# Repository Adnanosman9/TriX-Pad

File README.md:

<h1 align="center">
  TriXpad
</h1>

<h4 align="center">
  A custom, open-source mechanical macro-pad featuring an OLED screen.
</h4>

<div align="center">

</div>

<br>

##  Key Features

* **Brain:** Powered by the compact and capable **Seeed Studio XIAO RP2040**.
* **Firmware:** Runs on **KMK Firmware** (CircuitPython) for incredibly easy keymap customization without needing to recompile.
* **Display:** Integrated **0.91" SSD1306 OLED (128×64)** for real-time layer feedback, stats, or custom graphics.
* **Matrix:** A clean **3×3 Key Matrix** layout complete with diode orientation for robust anti-ghosting.

---

## Hardware Design

This project was built entirely from scratch, bridging custom PCB design with 3D modeling. 

### PCB (KiCad)
The board was routed and designed in KiCad to keep the footprint as minimal as possible while accommodating the XIAO RP2040 and OLED screen.

| Schematic | PCB Layout | 3D Render |
| :---: | :---: | :---: |
|  |  |  |

### Case (Fusion 360)
The enclosure was designed in Autodesk Fusion 360—marking my very first time diving into CAD! It features a sleek, two-part snap-fit/screw design to house the PCB and switches securely.

| Top Case | Bottom Case |
| :---: | :---: |
|  |  |

###  The Final Build
<div align="center">
  
</div>

---

##  Bill of Materials (BOM)

Everything you need to build this macro-pad yourself. *(For full details, see the [`BOM.csv`](BOM.csv) file).*

| Component | Description / Item | Qty | Source |
| :--- | :--- | :---: | :--- |
| **Controller** | Seeed Studio XIAO RP2040 | 1 | [AliExpress](https://www.aliexpress.com/item/1005003901735765.html) |
| **Switches** | MX-Style (Cherry) | 9 | [AliExpress](https://www.aliexpress.com/item/1005008656717678.html) |
| **Display** | 0.91" SSD1306 OLED | 1 | [AliExpress](https://www.aliexpress.com/item/1005009334190029.html) |
| **Diodes** | 1N4148 Through-Hole | 9 | [Robotics BD](https://store.roboticsbd.com/components/1355-1n4148-diode-robotics-bangladesh.html) |
| **Keycaps** | Blank DSA Keycaps (Black) | 9 | [AliExpress](https://www.aliexpress.com/item/1005006114411137.html) |

---

##  Credits & Acknowledgments

This project wouldn't be possible without these incredible open-source tools and communities:

* **[KiCad](https://www.kicad.org/)** for the phenomenal open-source PCB design suite.
* **[Autodesk Fusion 360](https://www.autodesk.com/products/fusion-360/)** for the case design environment.
* **[Hack Club Blueprint](https://blueprint.hackclub.com/)** for the guide and inspiration. 
* Massive thanks to **Hack Club Bank** for the grant that funded the PCB and case manufacturing to bring this hardware to life!

<br>

<div align="center">
  
  <br><br>
  <b>Designed by <a href="https://github.com/Adnanosman9">@Adnanosman</a></b>
</div>

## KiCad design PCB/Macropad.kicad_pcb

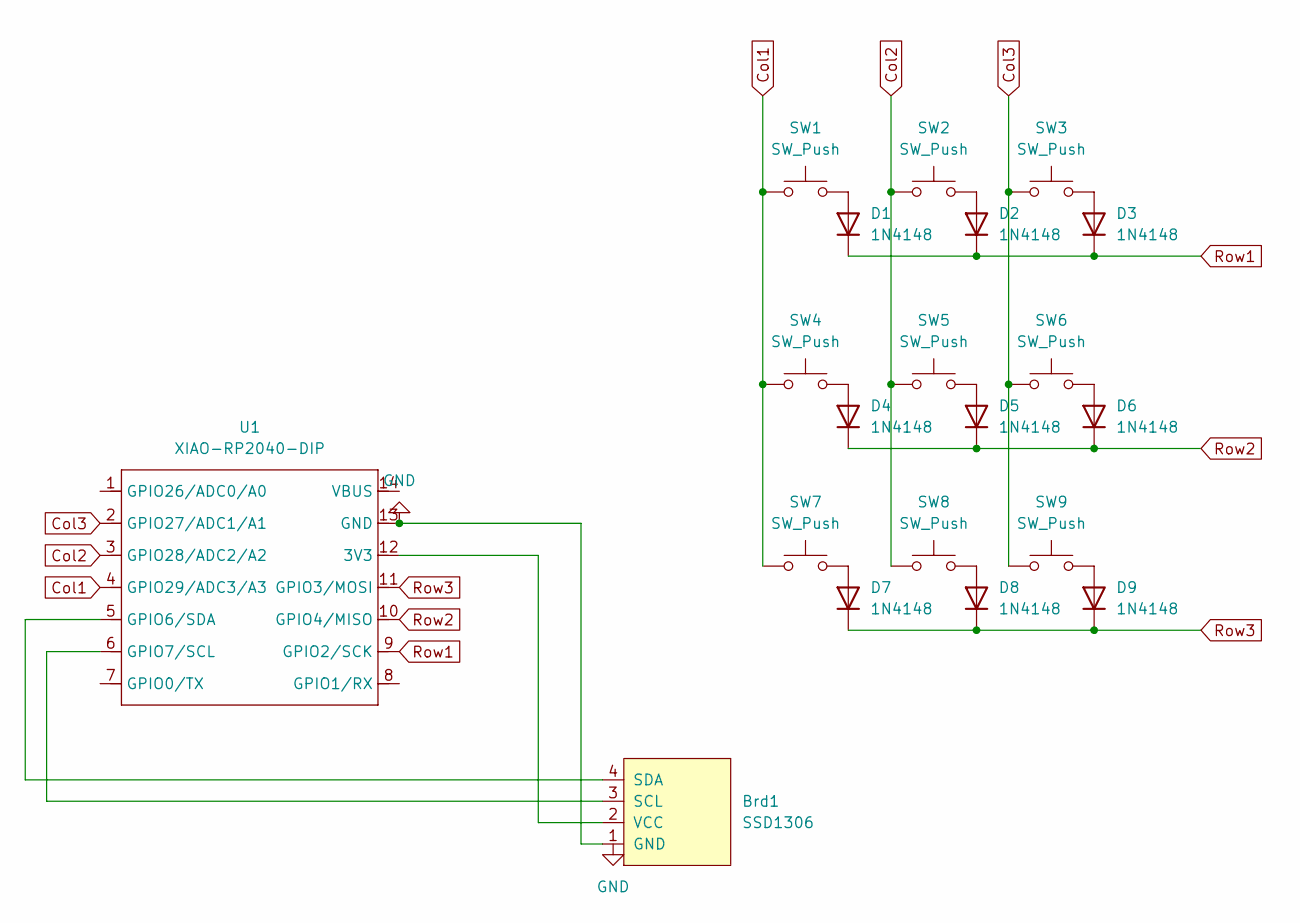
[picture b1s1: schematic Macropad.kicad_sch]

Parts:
Brd1: SSD1306; Adafruit_SSD1306
D1, D2, D3, D4, D5, D6, D7, D8, D9: 1N4148; D_DO-35_SOD27_P7.62mm_Horizontal
SW1, SW2, SW3, SW4, SW5, SW6, SW7, SW8, SW9: SW_Push; SW_Cherry_MX_1.00u_PCB
U1: XIAO-RP2040-DIP; Seeed_XIAO_RP2040

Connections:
Col1: SW1.1, SW4.1, SW7.1, U1.4 (GPIO29/ADC3/A3)
Col2: SW2.1, SW5.1, SW8.1, U1.3 (GPIO28/ADC2/A2)
Col3: SW3.1, SW6.1, SW9.1, U1.2 (GPIO27/ADC1/A1)
GND: Brd1.1 (GND), U1.13 (GND)
unnamed: Brd1.3 (SCL), U1.6 (GPIO7/SCL)
unnamed: Brd1.4 (SDA), U1.5 (GPIO6/SDA)
unnamed: Brd1.2 (VCC), U1.12 (3V3)
unnamed: D1.2 (A), SW1.2
unnamed: D2.2 (A), SW2.2
unnamed: D3.2 (A), SW3.2
unnamed: D4.2 (A), SW4.2
unnamed: D5.2 (A), SW5.2
unnamed: D6.2 (A), SW6.2
unnamed: D7.2 (A), SW7.2
unnamed: D8.2 (A), SW8.2
unnamed: D9.2 (A), SW9.2
Row1: D1.1 (K), D2.1 (K), D3.1 (K), U1.9 (GPIO2/SCK)
Row2: D4.1 (K), D5.1 (K), D6.1 (K), U1.10 (GPIO4/MISO)
Row3: D7.1 (K), D8.1 (K), D9.1 (K), U1.11 (GPIO3/MOSI)

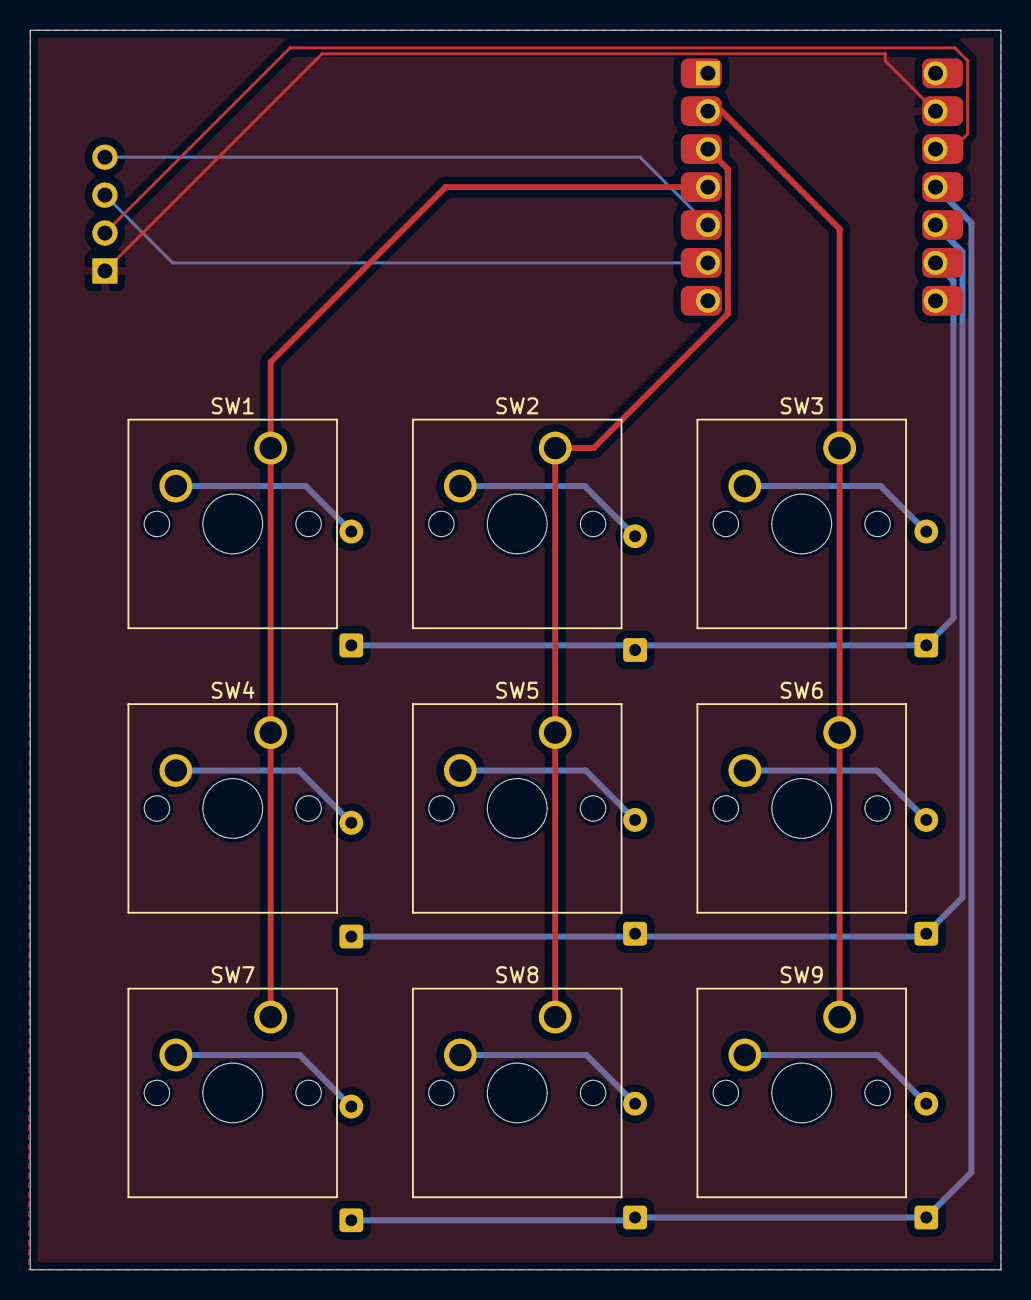
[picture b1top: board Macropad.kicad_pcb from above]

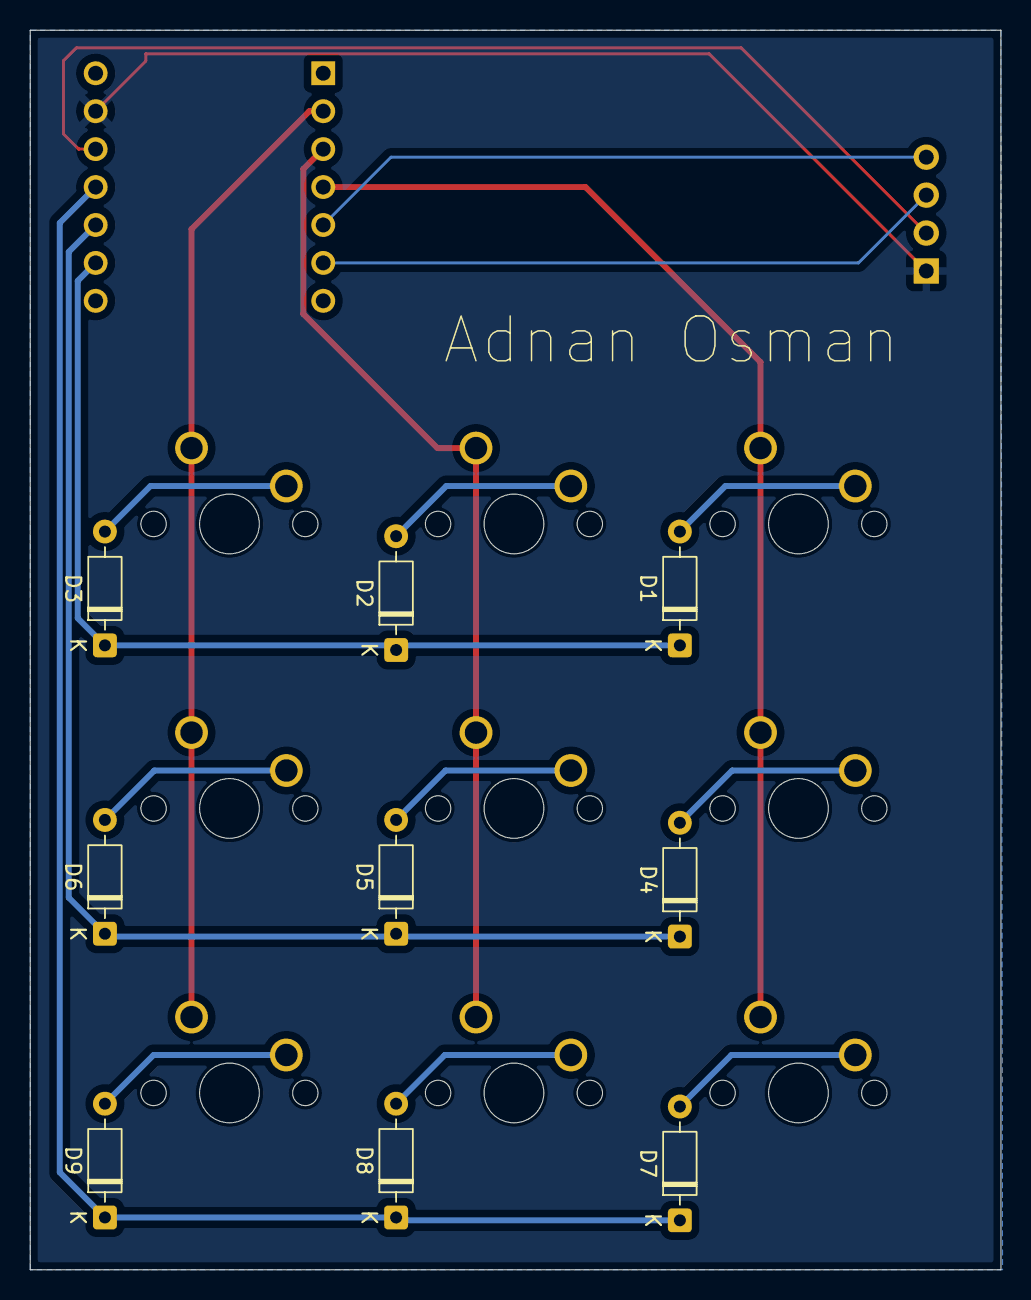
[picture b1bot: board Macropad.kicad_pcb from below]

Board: 2 copper layers, 65.0 x 83.0 mm, 20 parts (9 on the bottom side), 19 nets.

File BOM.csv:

Component,Item,Quantity,Link
Controller,Seeed Studio XIAO RP2040,1,https://www.aliexpress.com/item/1005003901735765.html?spm=a2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
Switches,MX-Style -Cherry,9,https://www.aliexpress.com/item/1005008656717678.html?spm=a2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
Display,"0.96"" SSD1306 OLED",1,https://www.aliexpress.com/item/1005008754404998.html?spm=a2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
Diodes,1N4148,9,https://store.roboticsbd.com/components/1355-1n4148-diode-ro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
Keycaps,Blank DSA Keycaps(Black),9,https://www.aliexpress.com/item/1005006114411137.html?spm=a2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
PCB,,1,https://www.nextpcb.com/?code=BanglaGECS
